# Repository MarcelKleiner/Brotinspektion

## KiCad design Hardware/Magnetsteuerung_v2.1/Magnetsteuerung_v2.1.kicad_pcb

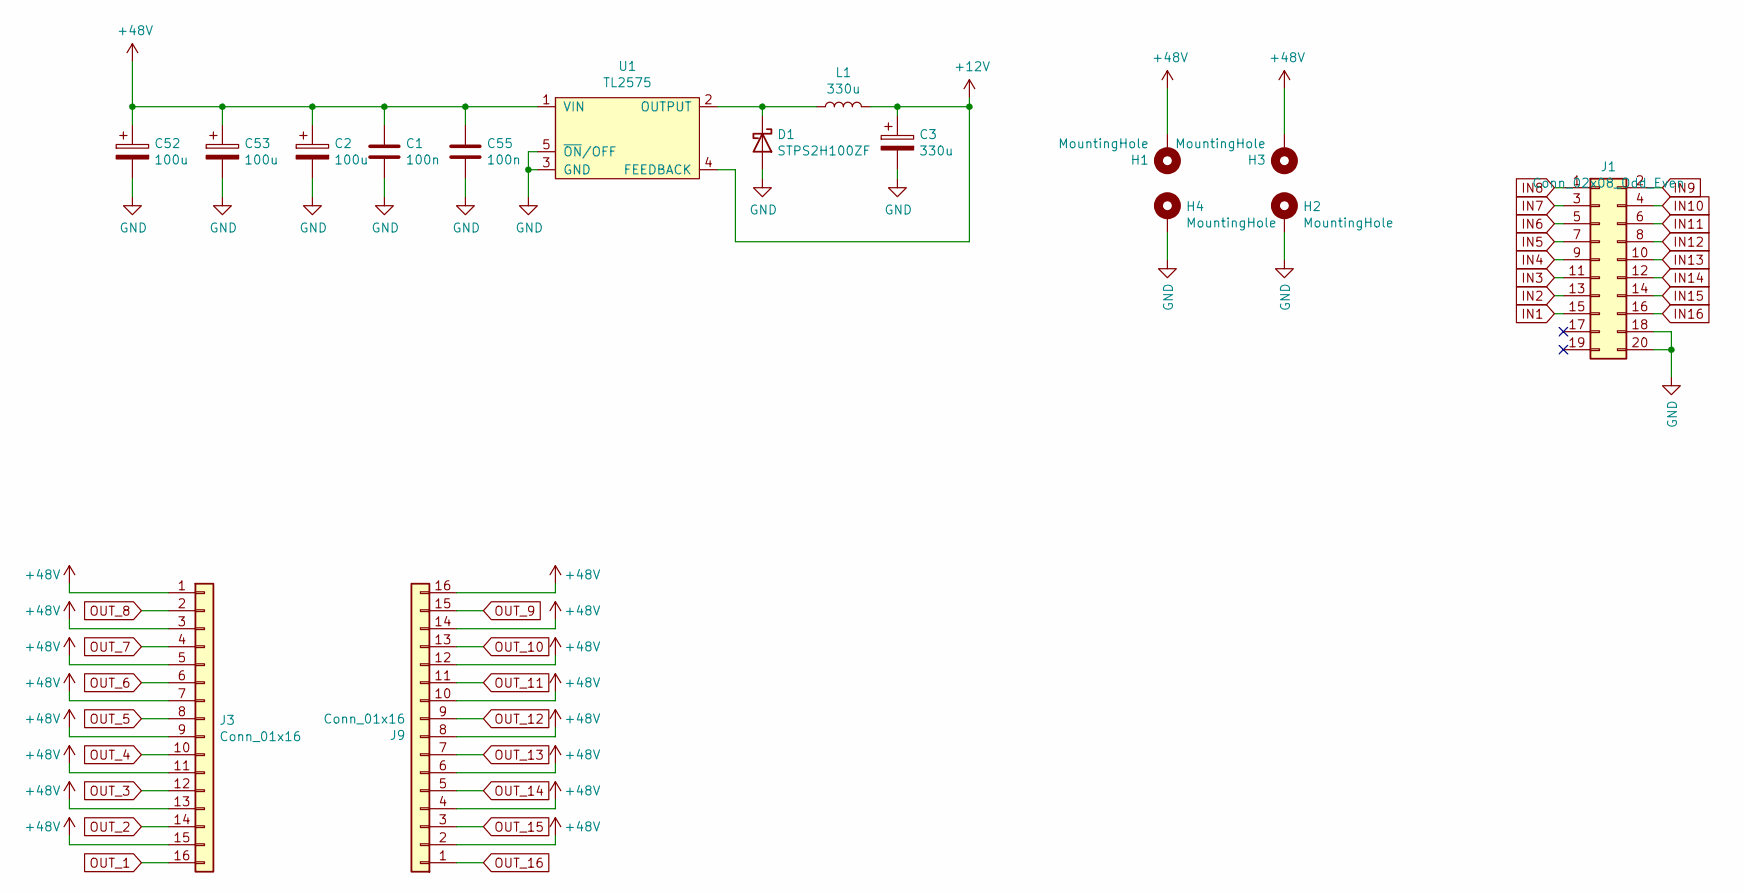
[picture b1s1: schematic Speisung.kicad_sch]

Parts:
C1, C55: 100n; C_1206_3216Metric
C2, C52, C53: 100u; CP_Elec_10x10
C3: 330u; CP_Elec_8x10
D1: STPS2H100ZF; D_SOD-123
H1, H2, H3, H4: MountingHole; MountingHole_4.3mm_M4_Pad_Via
J1: Conn_02x08_Odd_Even; PinHeader_2x10_P2.54mm_61202022021
J3, J9: Conn_01x16; PhoenixContact_MSTBA_2,5_16-G-5,08_1x16_P5.08mm_Horizontal
L1: 330u; L_Bourns_5050
U1: TL2575; TO-263-5_TabPin3

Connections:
+12V: C3.1, L1.2, U1.4 (FEEDBACK); also elsewhere on the board
+48V: C1.1, C2.1, C52.1, C53.1, C55.1, H1.1, H3.1, J3.1, J3.3, J3.5, J3.7, J3.9, J3.11, J3.13, J3.15, J9.2, J9.4, J9.6, J9.8, J9.10, J9.12, J9.14, J9.16, U1.1 (VIN); also elsewhere on the board
GND: C1.2, C2.2, C3.2, C52.2, C53.2, C55.2, D1.2 (A), H2.1, H4.1, J1.18, J1.20, U1.3 (GND), U1.5 (~ON/OFF); also elsewhere on the board
IN1: J1.15; also elsewhere on the board
IN2: J1.13; also elsewhere on the board
IN3: J1.11; also elsewhere on the board
IN4: J1.9; also elsewhere on the board
IN5: J1.7; also elsewhere on the board
IN6: J1.5; also elsewhere on the board
IN7: J1.3; also elsewhere on the board
IN8: J1.1; also elsewhere on the board
IN9: J1.2; also elsewhere on the board
IN10: J1.4; also elsewhere on the board
IN11: J1.6; also elsewhere on the board
IN12: J1.8; also elsewhere on the board
IN13: J1.10; also elsewhere on the board
IN14: J1.12; also elsewhere on the board
IN15: J1.14; also elsewhere on the board
IN16: J1.16; also elsewhere on the board
unnamed: D1.1 (K), L1.1, U1.2 (OUTPUT)
OUT_1: J3.16; also elsewhere on the board
OUT_2: J3.14; also elsewhere on the board
OUT_3: J3.12; also elsewhere on the board
OUT_4: J3.10; also elsewhere on the board
OUT_5: J3.8; also elsewhere on the board
OUT_6: J3.6; also elsewhere on the board
OUT_7: J3.4; also elsewhere on the board
OUT_8: J3.2; also elsewhere on the board
OUT_9: J9.15; also elsewhere on the board
OUT_10: J9.13; also elsewhere on the board
OUT_11: J9.11; also elsewhere on the board
OUT_12: J9.9; also elsewhere on the board
OUT_13: J9.7; also elsewhere on the board
OUT_14: J9.5; also elsewhere on the board
OUT_15: J9.3; also elsewhere on the board
OUT_16: J9.1; also elsewhere on the board

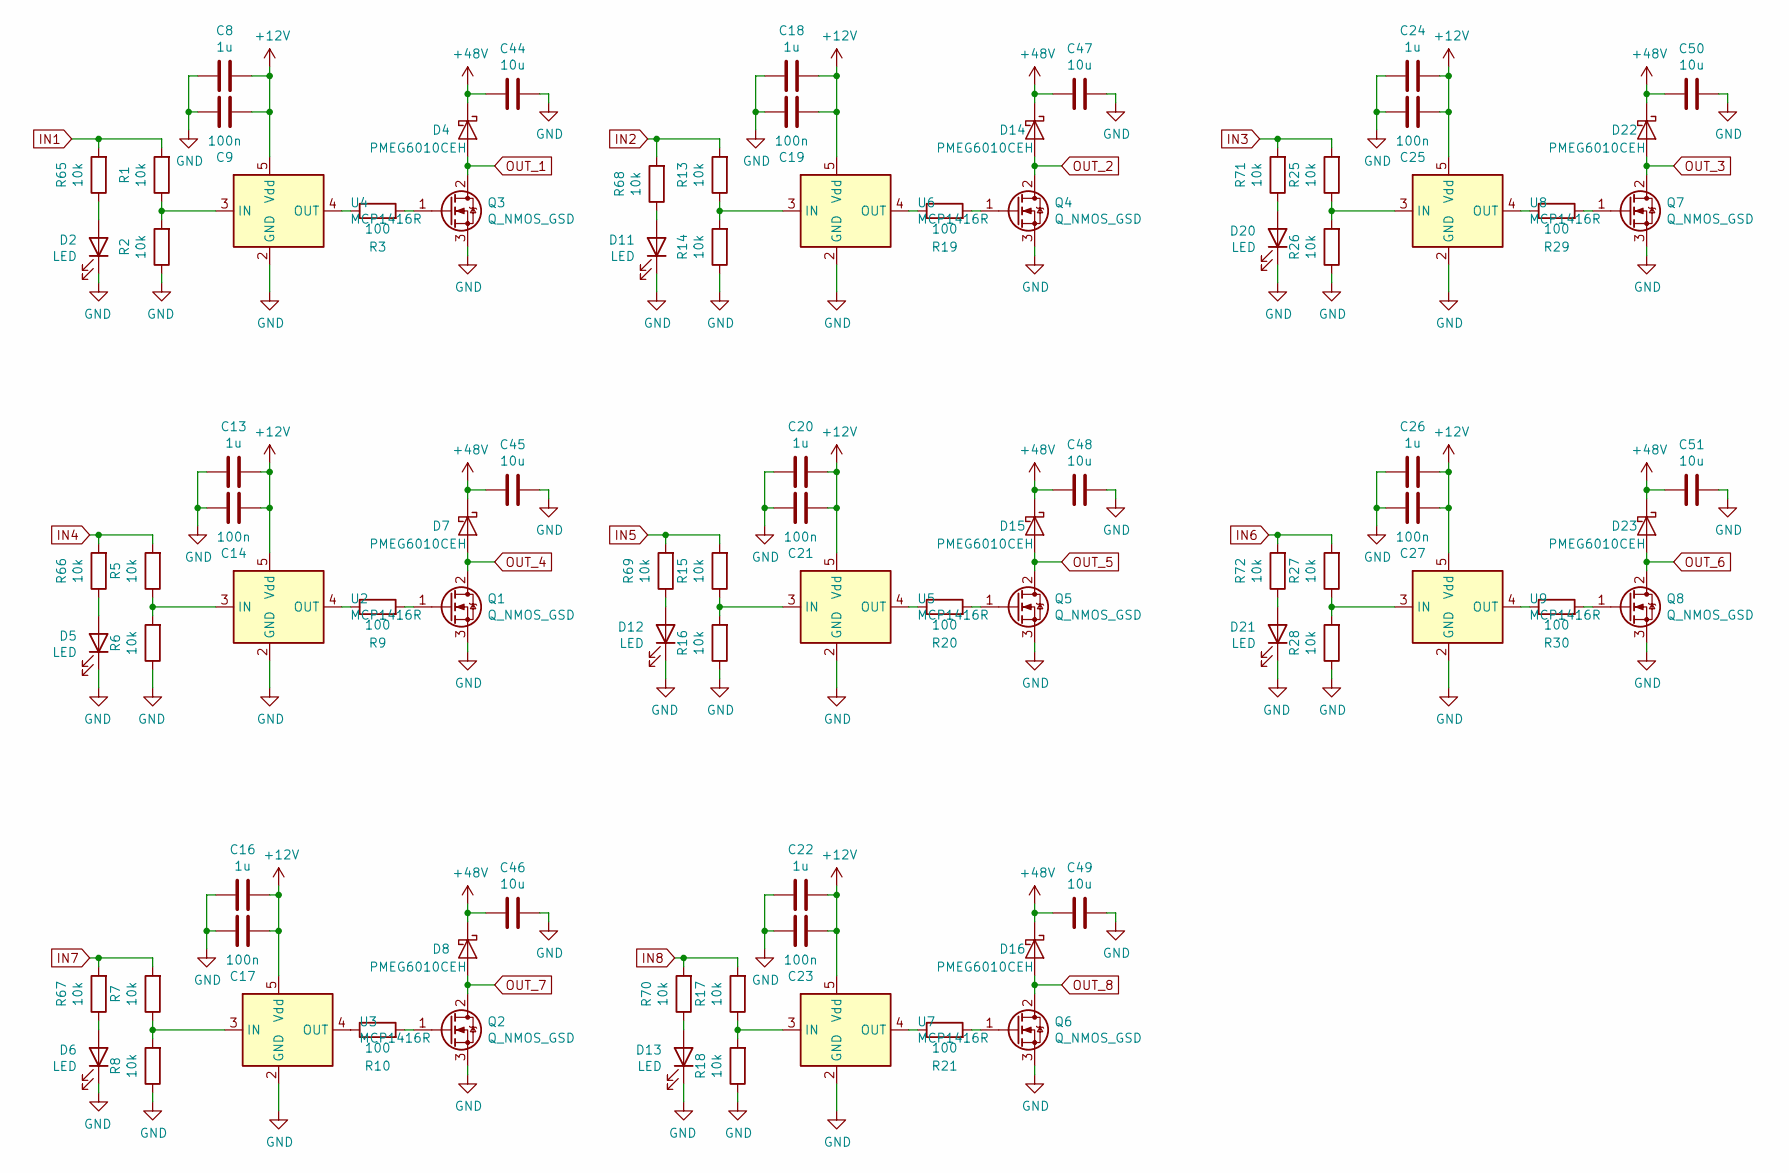
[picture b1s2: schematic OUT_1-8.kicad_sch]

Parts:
C8, C13, C16, C18, C20, C22, C24, C26: 1u; C_0603_1608Metric; Mouser Nr. 187-CL10B105KA8NNNC
C9, C14, C17, C19, C21, C23, C25, C27: 100n; C_0603_1608Metric; Mouser Nr. 710-885382206004
C44, C45, C46, C47, C48, C49, C50, C51: 10u; C_1210_3225Metric; Mouser Nr. 187-CL32B106KMVNNWE
D2, D5, D6, D11, D12, D13, D20, D21: LED; LED_0603_1608Metric; Mouser Nr. 710-150060VS55040
D4, D7, D8, D14, D15, D16, D22, D23: PMEG6010CEH; D_SOD_128_2; Mouser Nr. 771-PMEG6010CEH-QX
Q1, Q2, Q3, Q4, Q5, Q6, Q7, Q8: Q_NMOS_GSD; TO-252-2; Mouser Nr. 621-DMN10H220LK3-13
R1, R2, R5, R6, R7, R8, R13, R14, R15, R16, R17, R18, R25, R26, R27, R28, R65, R66, R67, R68, R69, R70, R71, R72: 10k; R_0603_1608Metric; Mouser Nr. 71-RCG060310K0FKEA
R3, R9, R10, R19, R20, R21, R29, R30: 100; R_0603_1608Metric; Mouser Nr. CRS0603AFX-1000ELF
U2, U3, U4, U5, U6, U7, U8, U9: MCP1416R; SOT-23-5; Mouser Nr. 579-MCP1416RT-E/OT

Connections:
+12V: C8.1, C9.1, C13.1, C14.1, C16.1, C17.1, C18.1, C19.1, C20.1, C21.1, C22.1, C23.1, C24.1, C25.1, C26.1, C27.1, U2.5 (Vdd), U3.5 (Vdd), U4.5 (Vdd), U5.5 (Vdd), U6.5 (Vdd), U7.5 (Vdd), U8.5 (Vdd), U9.5 (Vdd); also elsewhere on the board
+48V: C44.2, C45.2, C46.2, C47.2, C48.2, C49.2, C50.2, C51.2, D4.1 (K), D7.1 (K), D8.1 (K), D14.1 (K), D15.1 (K), D16.1 (K), D22.1 (K), D23.1 (K); also elsewhere on the board
GND: C8.2, C9.2, C13.2, C14.2, C16.2, C17.2, C18.2, C19.2, C20.2, C21.2, C22.2, C23.2, C24.2, C25.2, C26.2, C27.2, C44.1, C45.1, C46.1, C47.1, C48.1, C49.1, C50.1, C51.1, D2.1 (K), D5.1 (K), D6.1 (K), D11.1 (K), D12.1 (K), D13.1 (K), D20.1 (K), D21.1 (K), Q1.3 (S), Q2.3 (S), Q3.3 (S), Q4.3 (S), Q5.3 (S), Q6.3 (S), Q7.3 (S), Q8.3 (S), R2.1, R6.1, R8.1, R14.1, R16.1, R18.1, R26.1, R28.1, U2.2 (GND), U3.2 (GND), U4.2 (GND), U5.2 (GND), U6.2 (GND), U7.2 (GND), U8.2 (GND), U9.2 (GND); also elsewhere on the board
IN1: R1.2, R65.2; also elsewhere on the board
IN2: R13.2, R68.2; also elsewhere on the board
IN3: R25.2, R71.2; also elsewhere on the board
IN4: R5.2, R66.2; also elsewhere on the board
IN5: R15.2, R69.2; also elsewhere on the board
IN6: R27.2, R72.2; also elsewhere on the board
IN7: R7.2, R67.2; also elsewhere on the board
IN8: R17.2, R70.2; also elsewhere on the board
unnamed: D2.2 (A), R65.1
unnamed: D5.2 (A), R66.1
unnamed: D6.2 (A), R67.1
unnamed: D11.2 (A), R68.1
unnamed: D12.2 (A), R69.1
unnamed: D13.2 (A), R70.1
unnamed: D20.2 (A), R71.1
unnamed: D21.2 (A), R72.1
unnamed: Q1.1 (G), R9.2
unnamed: Q2.1 (G), R10.2
unnamed: Q3.1 (G), R3.2
unnamed: Q4.1 (G), R19.2
unnamed: Q5.1 (G), R20.2
unnamed: Q6.1 (G), R21.2
unnamed: Q7.1 (G), R29.2
unnamed: Q8.1 (G), R30.2
unnamed: R5.1, R6.2, U2.3 (IN)
unnamed: R9.1, U2.4 (OUT)
unnamed: R7.1, R8.2, U3.3 (IN)
unnamed: R10.1, U3.4 (OUT)
unnamed: R1.1, R2.2, U4.3 (IN)
unnamed: R3.1, U4.4 (OUT)
unnamed: R15.1, R16.2, U5.3 (IN)
unnamed: R20.1, U5.4 (OUT)
unnamed: R13.1, R14.2, U6.3 (IN)
unnamed: R19.1, U6.4 (OUT)
unnamed: R17.1, R18.2, U7.3 (IN)
unnamed: R21.1, U7.4 (OUT)
unnamed: R25.1, R26.2, U8.3 (IN)
unnamed: R29.1, U8.4 (OUT)
unnamed: R27.1, R28.2, U9.3 (IN)
unnamed: R30.1, U9.4 (OUT)
OUT_1: D4.2 (A), Q3.2 (D); also elsewhere on the board
OUT_2: D14.2 (A), Q4.2 (D); also elsewhere on the board
OUT_3: D22.2 (A), Q7.2 (D); also elsewhere on the board
OUT_4: D7.2 (A), Q1.2 (D); also elsewhere on the board
OUT_5: D15.2 (A), Q5.2 (D); also elsewhere on the board
OUT_6: D23.2 (A), Q8.2 (D); also elsewhere on the board
OUT_7: D8.2 (A), Q2.2 (D); also elsewhere on the board
OUT_8: D16.2 (A), Q6.2 (D); also elsewhere on the board

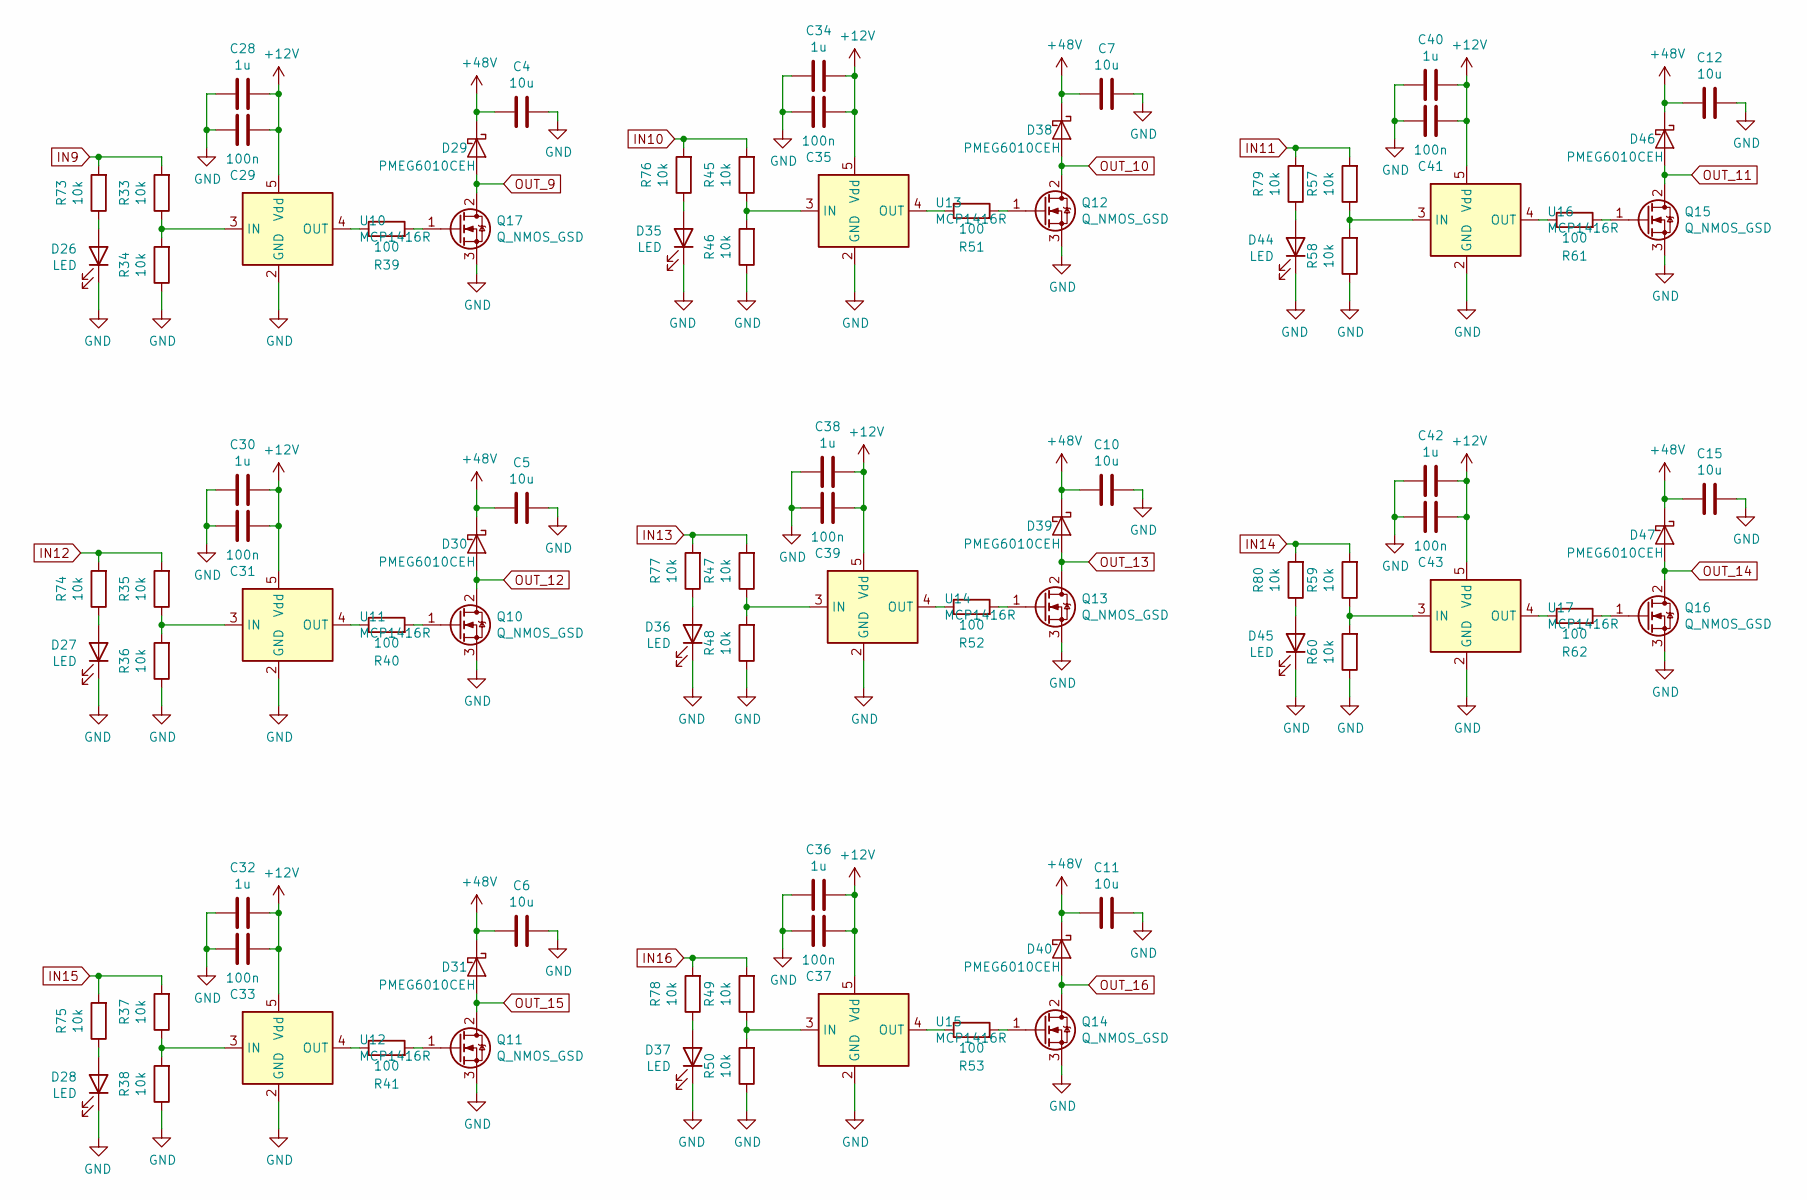
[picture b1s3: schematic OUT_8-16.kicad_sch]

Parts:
C4, C5, C6, C7, C10, C11, C12, C15: 10u; C_1210_3225Metric; Mouser Nr. 187-CL32B106KMVNNWE
C28, C30, C32, C34, C36, C38, C40, C42: 1u; C_0603_1608Metric; Mouser Nr. 187-CL10B105KA8NNNC
C29, C31, C33, C35, C37, C39, C41, C43: 100n; C_0603_1608Metric; Mouser Nr. 710-885382206004
D26, D27, D28, D35, D36, D37, D44, D45: LED; LED_0603_1608Metric; Mouser Nr. 710-150060VS55040
D29, D30, D31, D38, D39, D40, D46, D47: PMEG6010CEH; D_SOD_128_2; Mouser Nr. 771-PMEG6010CEH-QX
Q10, Q11, Q12, Q13, Q14, Q15, Q16, Q17: Q_NMOS_GSD; TO-252-2; Mouser Nr. 621-DMN10H220LK3-13
R33, R34, R35, R36, R37, R38, R45, R46, R47, R48, R49, R50, R57, R58, R59, R60, R73, R74, R75, R76, R77, R78, R79, R80: 10k; R_0603_1608Metric; Mouser Nr. 71-RCG060310K0FKEA
R39, R40, R41, R51, R52, R53, R61, R62: 100; R_0603_1608Metric; Mouser Nr. CRS0603AFX-1000ELF
U10, U11, U12, U13, U14, U15, U16, U17: MCP1416R; SOT-23-5; Mouser Nr. 579-MCP1416RT-E/OT

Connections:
+12V: C28.1, C29.1, C30.1, C31.1, C32.1, C33.1, C34.1, C35.1, C36.1, C37.1, C38.1, C39.1, C40.1, C41.1, C42.1, C43.1, U10.5 (Vdd), U11.5 (Vdd), U12.5 (Vdd), U13.5 (Vdd), U14.5 (Vdd), U15.5 (Vdd), U16.5 (Vdd), U17.5 (Vdd); also elsewhere on the board
+48V: C4.2, C5.2, C6.2, C7.2, C10.2, C11.2, C12.2, C15.2, D29.1 (K), D30.1 (K), D31.1 (K), D38.1 (K), D39.1 (K), D40.1 (K), D46.1 (K), D47.1 (K); also elsewhere on the board
GND: C4.1, C5.1, C6.1, C7.1, C10.1, C11.1, C12.1, C15.1, C28.2, C29.2, C30.2, C31.2, C32.2, C33.2, C34.2, C35.2, C36.2, C37.2, C38.2, C39.2, C40.2, C41.2, C42.2, C43.2, D26.1 (K), D27.1 (K), D28.1 (K), D35.1 (K), D36.1 (K), D37.1 (K), D44.1 (K), D45.1 (K), Q10.3 (S), Q11.3 (S), Q12.3 (S), Q13.3 (S), Q14.3 (S), Q15.3 (S), Q16.3 (S), Q17.3 (S), R34.1, R36.1, R38.1, R46.1, R48.1, R50.1, R58.1, R60.1, U10.2 (GND), U11.2 (GND), U12.2 (GND), U13.2 (GND), U14.2 (GND), U15.2 (GND), U16.2 (GND), U17.2 (GND); also elsewhere on the board
IN9: R33.2, R73.2; also elsewhere on the board
IN10: R45.2, R76.2; also elsewhere on the board
IN11: R57.2, R79.2; also elsewhere on the board
IN12: R35.2, R74.2; also elsewhere on the board
IN13: R47.2, R77.2; also elsewhere on the board
IN14: R59.2, R80.2; also elsewhere on the board
IN15: R37.2, R75.2; also elsewhere on the board
IN16: R49.2, R78.2; also elsewhere on the board
unnamed: D26.2 (A), R73.1
unnamed: D27.2 (A), R74.1
unnamed: D28.2 (A), R75.1
unnamed: D35.2 (A), R76.1
unnamed: D36.2 (A), R77.1
unnamed: D37.2 (A), R78.1
unnamed: D44.2 (A), R79.1
unnamed: D45.2 (A), R80.1
unnamed: Q10.1 (G), R40.2
unnamed: Q11.1 (G), R41.2
unnamed: Q12.1 (G), R51.2
unnamed: Q13.1 (G), R52.2
unnamed: Q14.1 (G), R53.2
unnamed: Q15.1 (G), R61.2
unnamed: Q16.1 (G), R62.2
unnamed: Q17.1 (G), R39.2
unnamed: R33.1, R34.2, U10.3 (IN)
unnamed: R39.1, U10.4 (OUT)
unnamed: R35.1, R36.2, U11.3 (IN)
unnamed: R40.1, U11.4 (OUT)
unnamed: R37.1, R38.2, U12.3 (IN)
unnamed: R41.1, U12.4 (OUT)
unnamed: R45.1, R46.2, U13.3 (IN)
unnamed: R51.1, U13.4 (OUT)
unnamed: R47.1, R48.2, U14.3 (IN)
unnamed: R52.1, U14.4 (OUT)
unnamed: R49.1, R50.2, U15.3 (IN)
unnamed: R53.1, U15.4 (OUT)
unnamed: R57.1, R58.2, U16.3 (IN)
unnamed: R61.1, U16.4 (OUT)
unnamed: R59.1, R60.2, U17.3 (IN)
unnamed: R62.1, U17.4 (OUT)
OUT_9: D29.2 (A), Q17.2 (D); also elsewhere on the board
OUT_10: D38.2 (A), Q12.2 (D); also elsewhere on the board
OUT_11: D46.2 (A), Q15.2 (D); also elsewhere on the board
OUT_12: D30.2 (A), Q10.2 (D); also elsewhere on the board
OUT_13: D39.2 (A), Q13.2 (D); also elsewhere on the board
OUT_14: D47.2 (A), Q16.2 (D); also elsewhere on the board
OUT_15: D31.2 (A), Q11.2 (D); also elsewhere on the board
OUT_16: D40.2 (A), Q14.2 (D); also elsewhere on the board

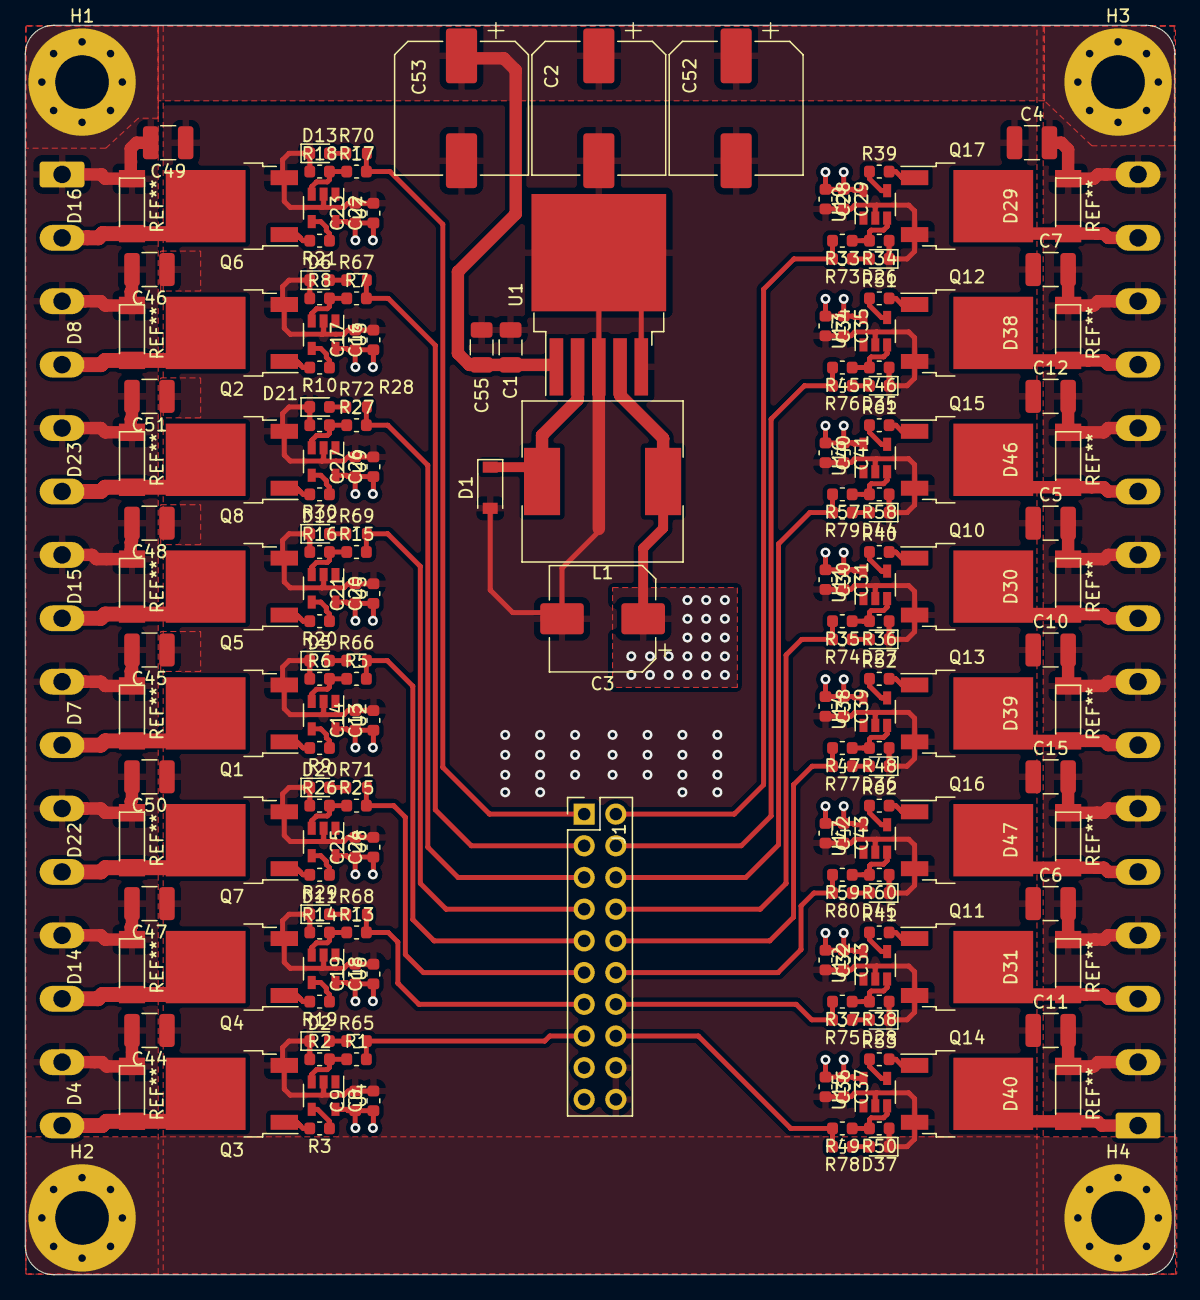
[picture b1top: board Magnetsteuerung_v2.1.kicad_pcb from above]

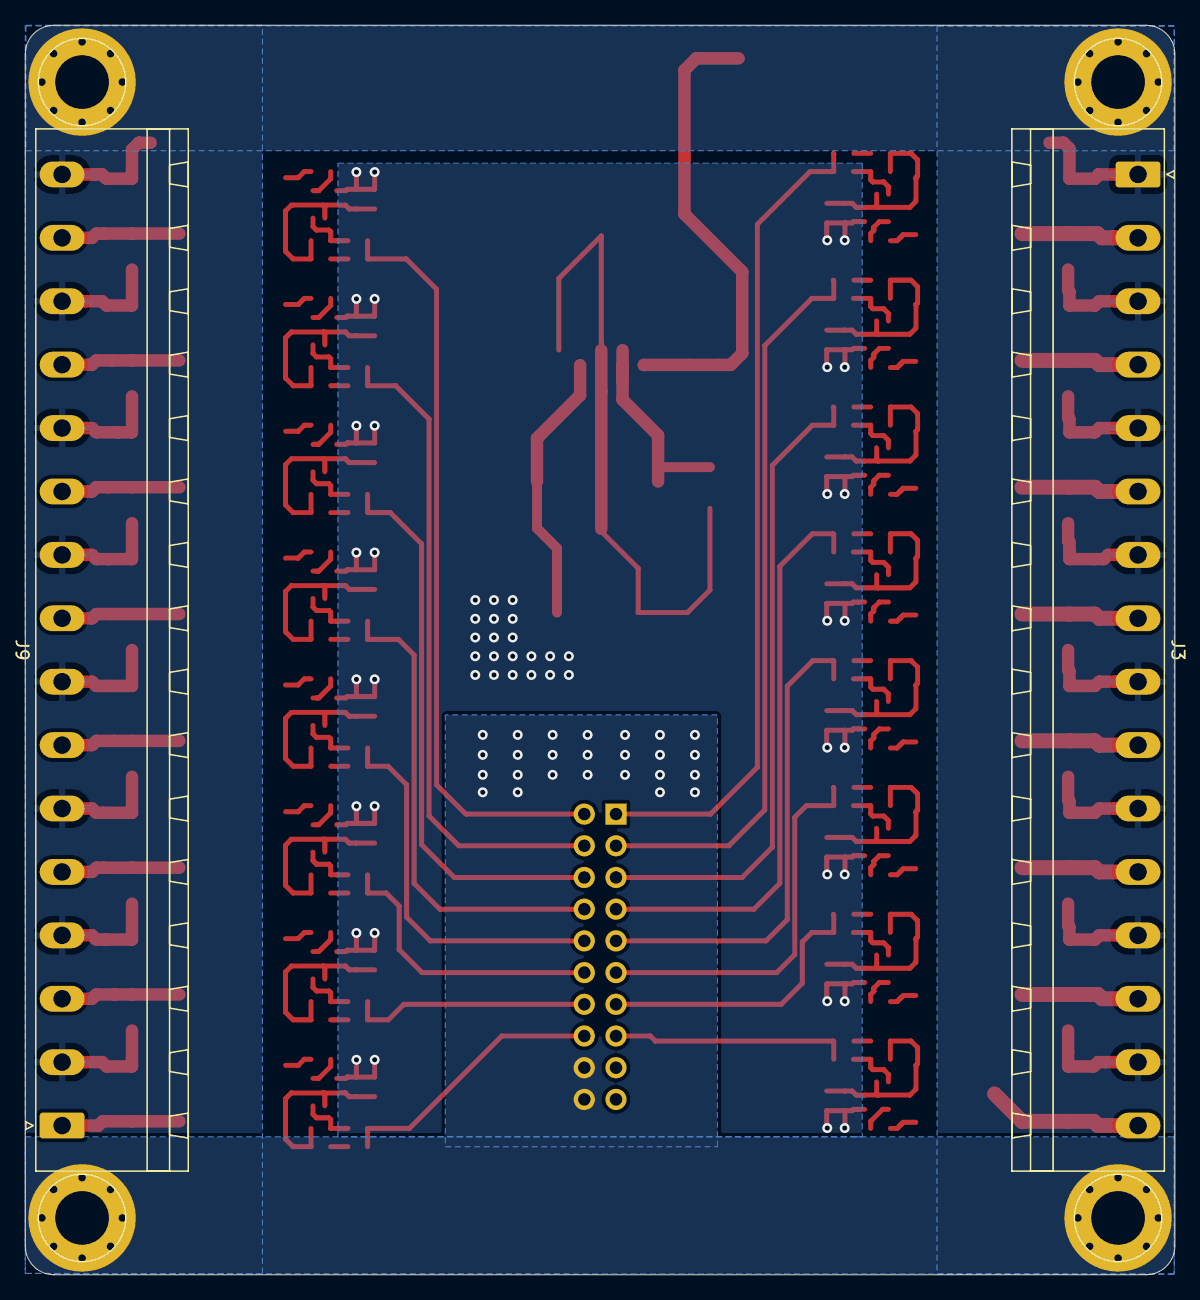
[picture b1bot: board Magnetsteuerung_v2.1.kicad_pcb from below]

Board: 2 copper layers, 92.1 x 100.1 mm, 192 parts (2 on the bottom side), 100 nets.

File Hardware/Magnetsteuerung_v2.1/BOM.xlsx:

Reference | Quantity | Value | Total
C1 C55 | 2 | 100n | 60 |  | 30
C16 C13 C8 C22 C20 C18 C26 C24 C28 C34 C40 C30 C38 C42 C32 C36 | 16 | 1u | 480
C2 C53 C52 | 3 | 100u | 90
C3 | 1 | 330u | 30
C44 C47 C50 C51 C48 C45 C46 C49 C4 C7 C12 C5 C10 C15 C6 C11 | 16 | 10u | 480
C9 C17 C14 C23 C21 C19 C27 C25 C29 C35 C41 C31 C39 C43 C33 C37 | 16 | 100n | 480
D1 | 1 | STPS2H100ZF | 30
D4 D29 D38 D46 D30 D39 D47 D31 D40 | 9 | PMEG6010CEH | 270
D6 D5 D2 D13 D12 D11 D20 D21 D26 D35 D44 D27 D36 D45 D28 D37 | 16 | LED | 480
D8 D7 D16 D15 D14 D23 D22 | 7 | PMEG6010CEH | 210
H1 H2 H3 H4 | 4 | MountingHole | 120
J1 | 1 | Conn_02x08_Odd_Even | 30
J3 J9 | 2 | Conn_01x16 | 60
L1 | 1 | 330u | 30
Q17 | 1 | Q_NMOS_GDS | 30
Q2 Q1 Q3 Q6 Q5 Q4 Q8 Q7 Q12 Q15 Q10 Q13 Q16 Q11 Q14 | 15 | Q_NMOS_GSD | 450
R10 R9 R3 R21 R20 R19 R30 R29 R39 R51 R61 R40 R52 R62 R41 R53 | 16 | 100 | 480
R67 R66 R65 R7 R8 R5 R6 R1 R2 R70 R69 R68 R17 R18 R15 R16 R13 R14 R71 R72 R27 R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 | 48 | 10k | 1440
U1 | 1 | TL2575 | 30
U3 U2 U4 U6 U5 U7 U9 U8 U10 U11 U12 U13 U14 U15 U16 U17 | 16 | MCP1416R | 480

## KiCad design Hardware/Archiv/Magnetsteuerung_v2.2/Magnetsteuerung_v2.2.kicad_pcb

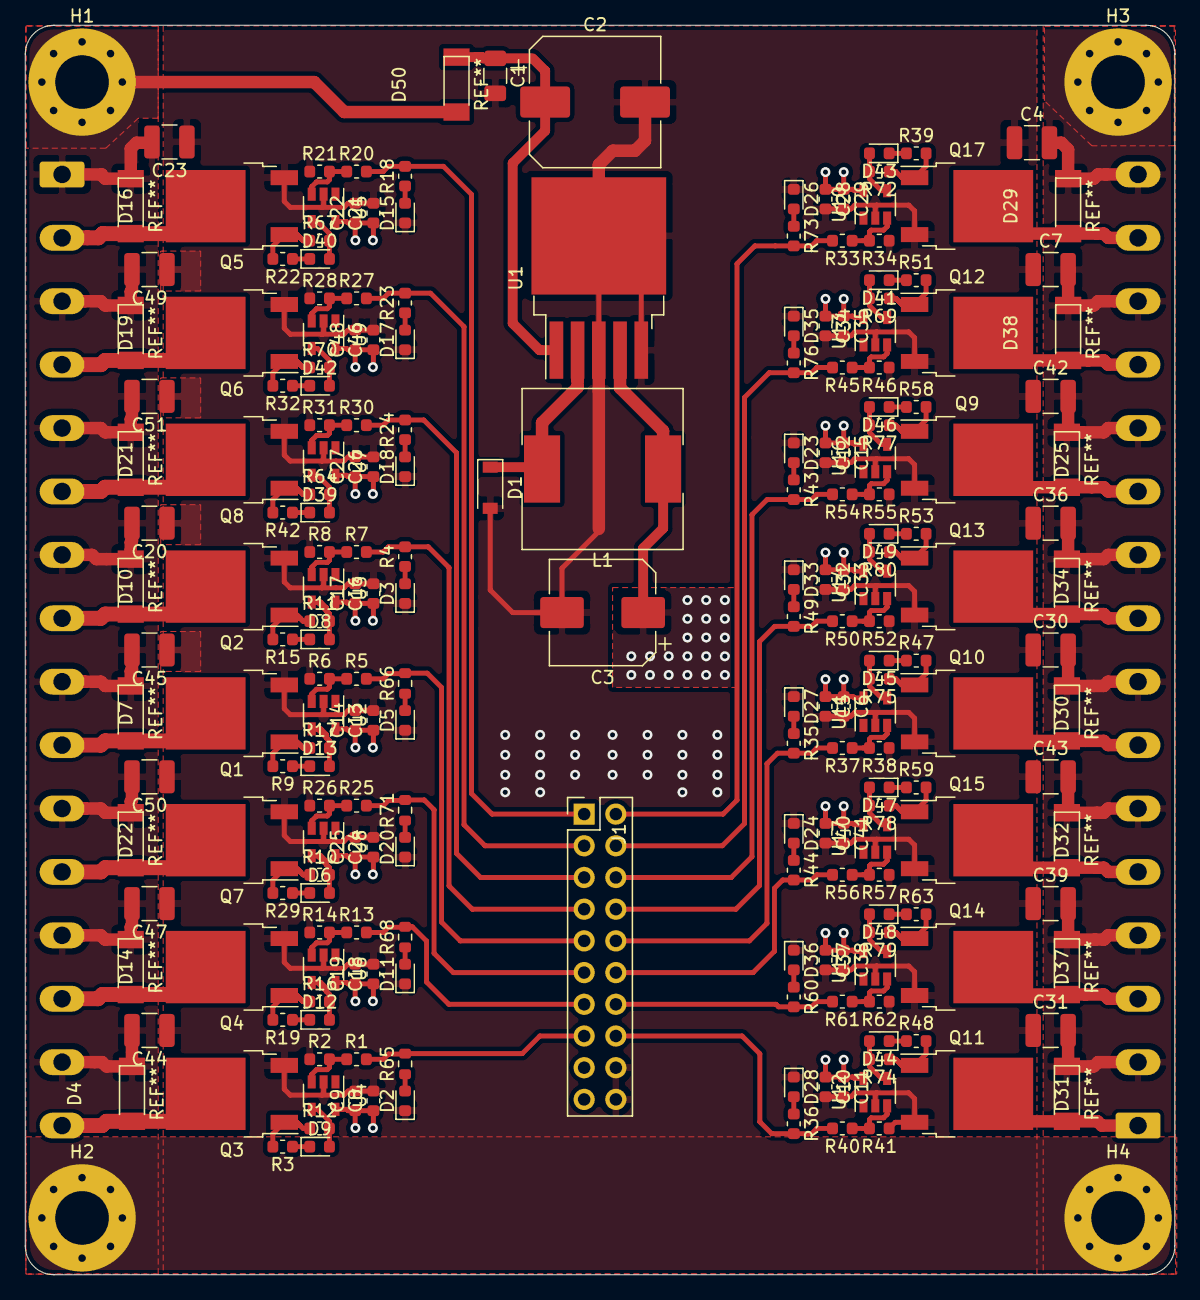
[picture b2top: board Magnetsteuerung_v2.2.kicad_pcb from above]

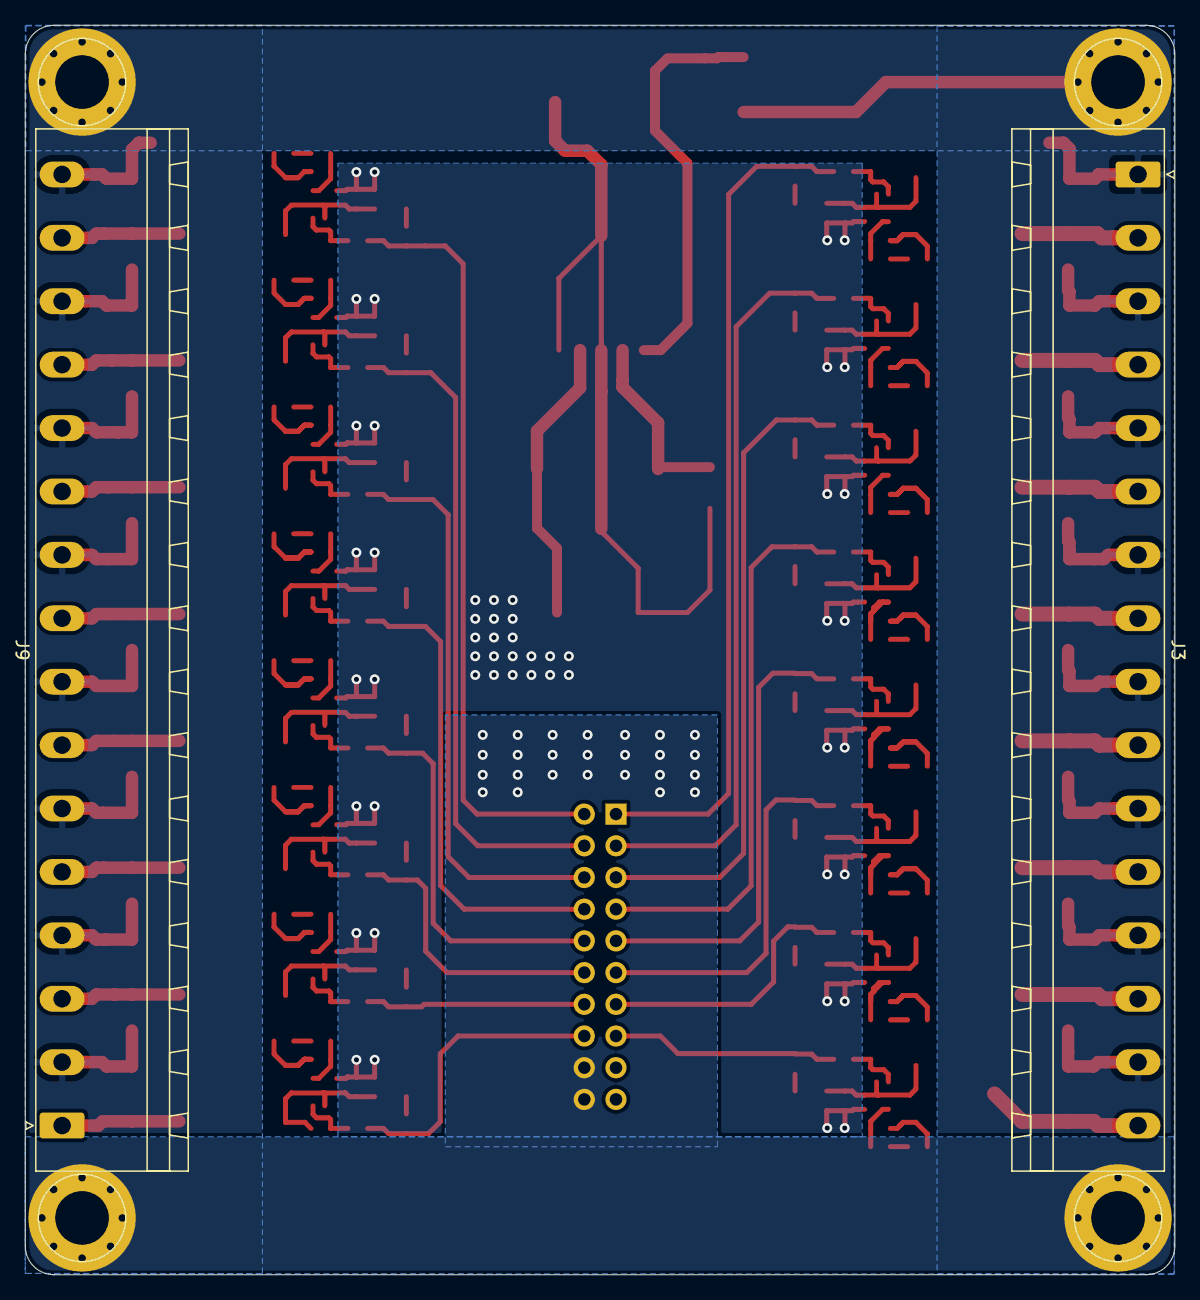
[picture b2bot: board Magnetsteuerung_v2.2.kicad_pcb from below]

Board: 2 copper layers, 92.1 x 100.1 mm, 222 parts (2 on the bottom side), 117 nets.

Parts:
C1: 100n; C_1206_3216Metric
C2: 100u; CP_Elec_10x10
C3: 330u; CP_Elec_8x10
C4, C7, C20, C23, C30, C31, C36, C39, C42, C43, C44, C45, C47, C49, C50, C51: 10u; C_1210_3225Metric
C5, C8, C10, C12, C13, C16, C18, C21, C24, C26, C28, C32, C34, C37, C40, C46: 1u; C_0603_1608Metric
C6, C9, C11, C14, C15, C17, C19, C22, C25, C27, C29, C33, C35, C38, C41, C48: 100n; C_0603_1608Metric
D1: STPS2H100ZF; D_SOD-123
D2, D3, D5, D11, D15, D17, D18, D20, D23, D24, D26, D27, D28, D33, D35, D36: LED; LED_0603_1608Metric
D4, D29, D38, D50: PMEG6010CEH; D_SOD_128_2
D6, D8, D9, D12, D13, D39, D40, D41, D42, D43, D44, D45, D46, D47, D48, D49: PMEG6010CEH; D_0603_1608Metric
D7, D10, D14, D16, D19, D21, D22, D25, D30, D31, D32, D34, D37: PMEG6010CEH; SOD_128
H1, H2, H3, H4: MountingHole; MountingHole_4.3mm_M4_Pad_Via
J1: Conn_02x08_Odd_Even; PinHeader_2x10_P2.54mm_61202022021
J3, J9: Conn_01x16; PhoenixContact_MSTBA_2,5_16-G-5,08_1x16_P5.08mm_Horizontal
L1: 330u; L_Bourns_5050
Q1, Q2, Q3, Q4, Q5, Q6, Q7, Q8, Q9, Q10, Q11, Q12, Q13, Q14, Q15: Q_NMOS_GSD; TO-252-2
Q17: Q_NMOS_GDS; TO-252-2
R1, R2, R4, R5, R6, R7, R8, R10, R11, R12, R13, R14, R16, R17, R18, R20, R21, R23, R24, R25, R26, R27, R28, R30, R31, R33, R34, R35, R36, R37, R38, R40, R41, R43, R44, R45, R46, R49, R50, R52, R54, R55, R56, R57, R60, R61, R62, R64, R65, R66, R67, R68, R69, R70, R71, R72, R73, R74, R75, R76, R77, R78, R79, R80: 10k; R_0603_1608Metric
R3, R9, R15, R19, R22, R29, R32, R39, R42, R47, R48, R51, R53, R58, R59, R63: 100; R_0603_1608Metric
U1: TL2575; TO-263-5_TabPin3
U2, U3, U4, U5, U6, U7, U8, U9, U10, U11, U12, U13, U14, U15, U16, U17: MCP1416R; SOT-23-5

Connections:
+12V: C3.1, C5.1, C6.1, C8.1, C9.1, C10.1, C11.1, C12.1, C13.1, C14.1, C15.1, C16.1, C17.1, C18.1, C19.1, C21.1, C22.1, C24.1, C25.1, C26.1, C27.1, C28.1, C29.1, C32.1, C33.1, C34.1, C35.1, C37.1, C38.1, C40.1, C41.1, C46.1, C48.1, L1.2, U1.4, U2.5, U3.5, U4.5, U5.5, U6.5, U7.5, U8.5, U9.5, U10.5, U11.5, U12.5, U13.5, U14.5, U15.5, U16.5, U17.5
+48V: C4.2, C7.2, C20.2, C23.2, C30.2, C31.2, C36.2, C39.2, C42.2, C43.2, C44.2, C45.2, C47.2, C49.2, C50.2, C51.2, D4.1, D7.1, D10.1, D14.1, D16.1, D19.1, D21.1, D22.1, D25.1, D29.1, D30.1, D31.1, D32.1, D34.1, D37.1, D38.1, D50.2, H1.1, H3.1, J3.1, J3.3, J3.5, J3.7, J3.9, J3.11, J3.13, J3.15, J9.2, J9.4, J9.6, J9.8, J9.10, J9.12, J9.14, J9.16
GND: C1.2, C2.2, C3.2, C4.1, C5.2, C6.2, C7.1, C8.2, C9.2, C10.2, C11.2, C12.2, C13.2, C14.2, C15.2, C16.2, C17.2, C18.2, C19.2, C20.1, C21.2, C22.2, C23.1, C24.2, C25.2, C26.2, C27.2, C28.2, C29.2, C30.1, C31.1, C32.2, C33.2, C34.2, C35.2, C36.1, C37.2, C38.2, C39.1, C40.2, C41.2, C42.1, C43.1, C44.1, C45.1, C46.2, C47.1, C48.2, C49.1, C50.1, C51.1, D1.2, D2.1, D3.1, D5.1, D11.1, D15.1, D17.1, D18.1, D20.1, D23.1, D24.1, D26.1, D27.1, D28.1, D33.1, D35.1, D36.1, H2.1, H4.1, J1.18, J1.20, Q1.3, Q2.3, Q3.3, Q4.3, Q5.3, Q6.3, Q7.3, Q8.3, Q9.3, Q10.3, Q11.3, Q12.3, Q13.3, Q14.3, Q15.3, Q17.3, R2.1, R6.1, R8.1, R14.1, R21.1, R26.1, R28.1, R31.1, R34.1, R38.1, R41.1, R46.1, R52.1, R55.1, R57.1, R62.1, U1.3, U1.5, U2.2, U3.2, U4.2, U5.2, U6.2, U7.2, U8.2, U9.2, U10.2, U11.2, U12.2, U13.2, U14.2, U15.2, U16.2, U17.2
IN1: J1.15, R1.2, R65.2
IN2: J1.13, R13.2, R68.2
IN3: J1.11, R25.2, R71.2
IN4: J1.9, R5.2, R66.2
IN5: J1.7, R4.2, R7.2
IN6: J1.5, R24.2, R30.2
IN7: J1.3, R23.2, R27.2
IN8: J1.1, R18.2, R20.2
IN9: J1.2, R33.2, R73.2
IN10: J1.4, R45.2, R76.2
IN11: J1.6, R43.2, R54.2
IN12: J1.8, R49.2, R50.2
IN13: J1.10, R35.2, R37.2
IN14: J1.12, R44.2, R56.2
IN15: J1.14, R60.2, R61.2
IN16: J1.16, R36.2, R40.2
unnamed: C1.1, C2.1, D50.1, U1.1
unnamed: D1.1, L1.1, U1.2
unnamed: D2.2, R65.1
unnamed: D3.2, R4.1
unnamed: D5.2, R66.1
unnamed: D6.1, R29.1
unnamed: D6.2, R10.2, U8.4
unnamed: D8.1, R15.1
unnamed: D8.2, R11.2, U3.4
unnamed: D9.1, R3.1
unnamed: D9.2, R12.2, U4.4
unnamed: D11.2, R68.1
unnamed: D12.1, R19.1
unnamed: D12.2, R16.2, U6.4
unnamed: D13.1, R9.1
unnamed: D13.2, R17.2, U2.4
unnamed: D15.2, R18.1
unnamed: D17.2, R23.1
unnamed: D18.2, R24.1
unnamed: D20.2, R71.1
unnamed: D23.2, R43.1
unnamed: D24.2, R44.1
unnamed: D26.2, R73.1
unnamed: D27.2, R35.1
unnamed: D28.2, R36.1
unnamed: D33.2, R49.1
unnamed: D35.2, R76.1
unnamed: D36.2, R60.1
unnamed: D39.1, R42.1
unnamed: D39.2, R64.2, U7.4
unnamed: D40.1, R22.1
unnamed: D40.2, R67.2, U5.4
unnamed: D41.1, R51.1
unnamed: D41.2, R69.2, U13.4
unnamed: D42.1, R32.1
unnamed: D42.2, R70.2, U9.4
unnamed: D43.1, R39.1
unnamed: D43.2, R72.2, U10.4
unnamed: D44.1, R48.1
unnamed: D44.2, R74.2, U12.4
unnamed: D45.1, R47.1
unnamed: D45.2, R75.2, U11.4
unnamed: D46.1, R58.1
unnamed: D46.2, R77.2, U16.4
unnamed: D47.1, R59.1
unnamed: D47.2, R78.2, U17.4
unnamed: D48.1, R63.1
unnamed: D48.2, R79.2, U15.4
unnamed: D49.1, R53.1
unnamed: D49.2, R80.2, U14.4
unnamed: Q1.1, R9.2, R17.1
unnamed: Q2.1, R11.1, R15.2
unnamed: Q3.1, R3.2, R12.1
unnamed: Q4.1, R16.1, R19.2
unnamed: Q5.1, R22.2, R67.1
unnamed: Q6.1, R32.2, R70.1
unnamed: Q7.1, R10.1, R29.2
unnamed: Q8.1, R42.2, R64.1
unnamed: Q9.1, R58.2, R77.1
unnamed: Q10.1, R47.2, R75.1
unnamed: Q11.1, R48.2, R74.1
unnamed: Q12.1, R51.2, R69.1
unnamed: Q13.1, R53.2, R80.1
unnamed: Q14.1, R63.2, R79.1
unnamed: Q15.1, R59.2, R78.1
unnamed: Q17.1, R39.2, R72.1
unnamed: R1.1, R2.2, U4.3
unnamed: R5.1, R6.2, U2.3
unnamed: R7.1, R8.2, U3.3
unnamed: R13.1, R14.2, U6.3
unnamed: R20.1, R21.2, U5.3
unnamed: R25.1, R26.2, U8.3
unnamed: R27.1, R28.2, U9.3
unnamed: R30.1, R31.2, U7.3
unnamed: R33.1, R34.2, U10.3
unnamed: R37.1, R38.2, U11.3
unnamed: R40.1, R41.2, U12.3
unnamed: R45.1, R46.2, U13.3
unnamed: R50.1, R52.2, U14.3
unnamed: R54.1, R55.2, U16.3
unnamed: R56.1, R57.2, U17.3
unnamed: R61.1, R62.2, U15.3
OUT_1: D4.2, J3.16, Q3.2
OUT_2: D14.2, J3.14, Q4.2
OUT_3: D22.2, J3.12, Q7.2
OUT_4: D7.2, J3.10, Q1.2
OUT_5: D10.2, J3.8, Q2.2
OUT_6: D21.2, J3.6, Q8.2
OUT_7: D19.2, J3.4, Q6.2
OUT_8: D16.2, J3.2, Q5.2
OUT_9: D29.2, J9.15, Q17.2
OUT_10: D38.2, J9.13, Q12.2
OUT_11: D25.2, J9.11, Q9.2
OUT_12: D34.2, J9.9, Q13.2
OUT_13: D30.2, J9.7, Q10.2
OUT_14: D32.2, J9.5, Q15.2
OUT_15: D37.2, J9.3, Q14.2
OUT_16: D31.2, J9.1, Q11.2

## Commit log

2021-05-21 update layout
2021-05-21 update gitignore //stp, iam, ipt
2021-06-11 add Layout v2.1
2021-06-13 Add V2.1
2021-06-18 update HW, supply over mounting hole
2021-06-21 change HW
2021-06-21 Change wire thiknes
2021-06-25 add v2.2
2021-07-24 fertigungsdaten aufbereitet
2023-06-29 change hardware
2023-06-29 Finalisierung
